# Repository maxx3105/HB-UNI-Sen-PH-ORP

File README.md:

# HB-UNI-Sen-PH-ORP
HomeMatic PH- und Redox-Sensor

Dieses Projekt basiert auf der Arbeit von [pa-pa](https://github.com/pa-pa/AskSinPP) ,[Jérôme](https://github.com/jp112sdl/Beispiel_AskSinPP).

# Hardware

### Bauteile

Bauteile                   | Bezeichnung          | Anzahl | Kommentar   | 
-------------------------- | -------------------- | ------ | ----------- | 
R1,R2                      | 30K Ohm              |   2    |             |
R3                         | 75K Ohm              |   1    |             |
R4                         | 1,5K Ohm             |   1    |             |
R5,R6                      | 10K Ohm              |   2    |             |
SR1                        | 1K Ohm               |   1    |  [ELV.de](https://de.elv.com/sicherungswiderstand-1k-091814?fs=1418091890)           |
C1,C2                      | 150 µF               |   2    |             |
C3,C4,C6                   | 0,1 µF               |   3    |             |
C5,C7                      | 10 µF                |   2    |             |
D1                         | SMD LED Rot          |   1    |             |
SW1                        | Taster               |   1    | [Aliexpress](https://de.aliexpress.com/item/32660690016.html?spm=a2g0s.9042311.0.0.27424c4dqj9wVN)            |
PS1                        | HLK-PM01             |   1    |             |
X1                         | WAGO 236-403         |   1    |             |
U1                         | Arduino MiniPro 3,3V |   1    |             |
U2                         | CC1101               |   1    | [Aliexpress](https://de.aliexpress.com/item/32924239954.html) |
U3                         | LM2660M              |   1    |             |
U4                         | LM358M               |   1    |             |
RV1                        | Varistor             |   1    |             |

#### Sonstiges

~8,3 cm Draht als Antenne

### Programmieradapter

- 1x FTDI Programmer https://www.az-delivery.de/products/ftdi-adapter-ft232rl

# Software

https://www.arduino.cc/en/software

### Firmware

Sketch https://github.com/jp112sdl/HB-UNI-Sen-PH-ORP/blob/master/HB-UNI-Sen-PH-ORP.ino

# Bauanleitung

coming soon

# Bilder

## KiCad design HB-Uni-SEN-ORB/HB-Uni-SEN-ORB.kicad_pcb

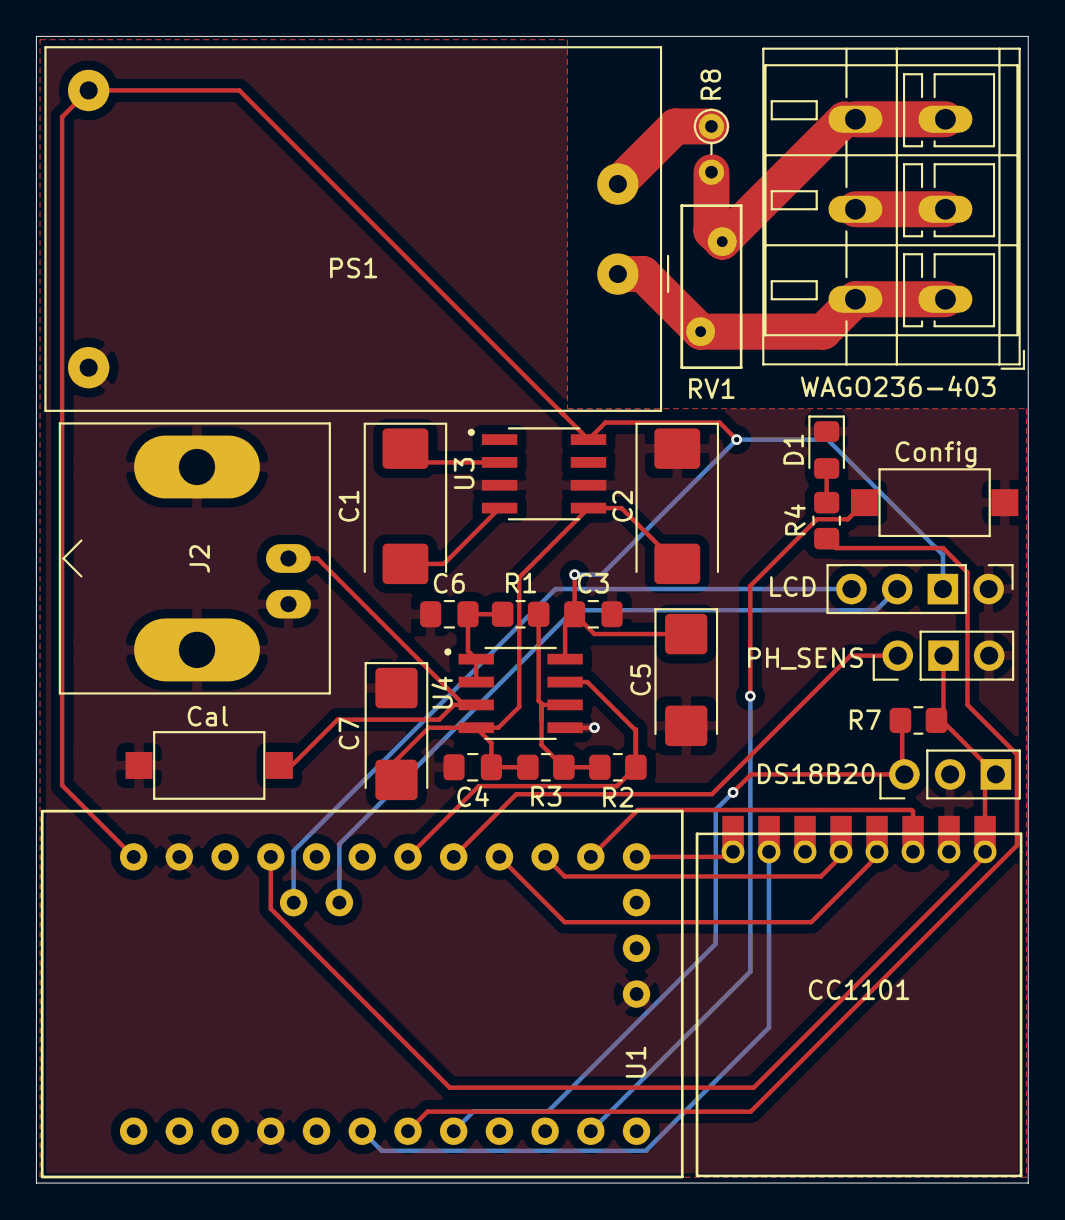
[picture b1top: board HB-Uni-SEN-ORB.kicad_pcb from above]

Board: 2 copper layers, 55.1 x 63.7 mm, 27 parts (0 on the bottom side), 25 nets.

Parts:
C1, C2: 150µF; CP_EIA-7343-15_Kemet-W_Pad2.25x2.55mm_HandSolder
C3, C4, C6: 0.1µF; C_0805_2012Metric_Pad1.18x1.45mm_HandSolder
C5: 10µF; CP_EIA-6032-15_Kemet-U_Pad2.25x2.35mm_HandSolder
C7: 10µF; CP_EIA-6032-28_Kemet-C_Pad2.25x2.35mm_HandSolder
Cal: CAL; SW_SPST_CK_RS282G05A3
Config: CONFIG; SW_SPST_CK_RS282G05A3
D1: LED; LED_0805_2012Metric_Pad1.15x1.40mm_HandSolder
DS18B20: DS18B20; PinHeader_1x03_P2.54mm_Vertical
J2: BNC; BNC_Amphenol_B6252HB-NPP3G-50_Horizontal
LCD: LCD; PinHeader_1x04_P2.54mm_Vertical
PH_SENS: PH_SENSOR; PinHeader_1x03_P2.54mm_Vertical
PS1: HLK-PM01; Converter_ACDC_HiLink_HLK-PMxx
R1, R2: 30K; R_0805_2012Metric_Pad1.20x1.40mm_HandSolder
R3: 75K; R_0805_2012Metric_Pad1.20x1.40mm_HandSolder
R4: 1.5K; R_0805_2012Metric_Pad1.20x1.40mm_HandSolder
R7: 4.7K; R_0805_2012Metric_Pad1.20x1.40mm_HandSolder
R8: SR1K; R_Axial_DIN0204_L3.6mm_D1.6mm_P2.54mm_Vertical
RV1: Varistor; RV_Disc_D9mm_W3.3mm_P5mm
U1: Arduino_Pro_Mini
U2: CC1101; CC1101_SMD_THT_Ohne_Ant
U3: LM2660M; SOIC127P599X175-8N
U4: LM358M_NOPB; SOIC127P599X175-8N
WAGO236-403: WAGO 236-403; TerminalBlock_WAGO_236-403_1x03_P5.00mm_45Degree

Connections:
+5V: C3.1, C5.1, LCD.2, PS1.4, U1.RAW, U3.8, U4.8
-5V: C2.2, C4.1, C7.2, R3.2, U3.5, U4.4
/1_WIRE: DS18B20.1, R7.2, U1.5
/A0: PH_SENS.1, U1.A0
/A1: R2.2, U1.A1, U4.7
/CONFIG: Config.2, U1.8
/CSN: U1.10, U2.8
/GDO0: U1.3, U2.7
/LED: R4.2, U1.4
/MISO: U1.12, U2.5
/MOSI: U1.11, U2.3
/SCK: U1.13, U2.4
/SCL: LCD.4, U1.A5
/SDA: LCD.3, U1.A4
/VCC: DS18B20.3, PH_SENS.2, R7.1, U1.VCC, U2.1
GND: C2.1, C3.2, C4.2, C5.2, C6.1, C7.1, Cal.1, Config.1, D1.1, DS18B20.2, J2.2, LCD.1, PH_SENS.3, PS1.3, U1.GND, U2.2, U3.3, U3.6, U4.5
unnamed: C1.1, U3.2
unnamed: C1.2, U3.4
unnamed: C6.2, R1.2, U4.1, U4.2
unnamed: Cal.2, J2.1, U4.3
unnamed: D1.2, R4.1
unnamed: PS1.2, R8.1
unnamed: PS1.1, RV1.1, WAGO236-403.1
unnamed: R1.1, R2.1, R3.1, U4.6
unnamed: R8.2, RV1.2, WAGO236-403.3

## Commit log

2021-04-26 Update README.md
    Add I2C Pullup
2021-04-26 Add files via upload
    Add I2C Pullup
